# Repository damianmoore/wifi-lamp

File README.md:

# WiFi Lamp

A simple wifi-enabled lamp control board based on the ESP8266. It is intended
primarily to help retrofit existing LED lamps, giving them switching and dimming
functionality through a web browser or home automation system.

The project is based around the ESP8266-01 module as it is widely available,
small, very cheap, easily programmable, and directly connects to your existing
wifi network.

The included electronics files (schematic and PCB layout) are designed in KiCad.

An RS-232 USB-to-serial convertor is required for programming. If you use this
adaptor to power the device while programming, it must output 3.3V (not higher).

## Specifications

 * Input voltage: **3.3 – 15V**
 * LED PWM dimmer frequency: **1000 Hz**

## Components (BOM)

 * ESP8266-01 module
 * AMS1117 3.3V voltage regulator, SOT-223 package
 * BCP53 transistor, SOT-223 package
 * 2 × SMD SPST switches, ~6mm wide × ~3mm deep
 * Row of 4 header pins

## Renderings

## Schematic

## Overview of the layers used for PCB production

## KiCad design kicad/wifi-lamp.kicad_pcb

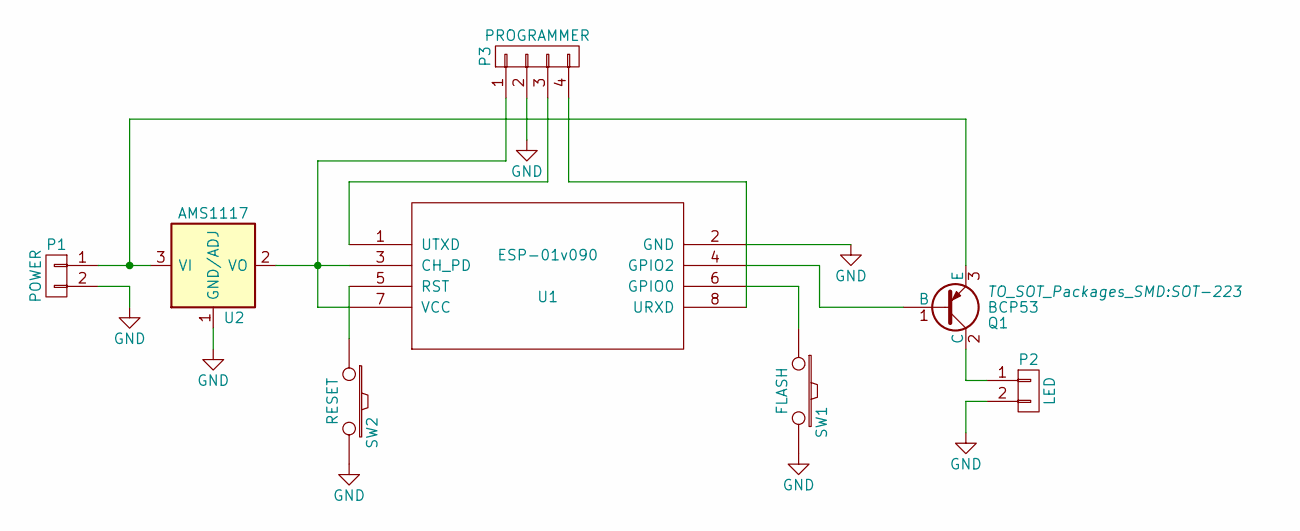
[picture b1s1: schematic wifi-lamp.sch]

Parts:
P1: POWER; WireConnection_1.50mmDrill
P2: LED; WireConnection_1.50mmDrill
P3: PROGRAMMER; Pin_Header_Straight_1x04
Q1: BCP53; SOT-223
SW1: FLASH; SW_SPST_REED_CT05-XXXX-G1
SW2: RESET; SW_SPST_REED_CT05-XXXX-G1
U1: ESP-01v090; ESP-01
U2: AMS1117; SOT-223

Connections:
GND: P1.2, P2.2, P3.2, SW1.2, SW2.2, U1.2 (GND), U2.1 (GND/ADJ)
unnamed: P1.1, Q1.3 (E), U2.3 (VI)
unnamed: P2.1, Q1.2 (C)
unnamed: P3.1, U1.3 (CH_PD), U1.7 (VCC), U2.2 (VO), U2.4 (VO)
unnamed: P3.3, U1.1 (UTXD)
unnamed: P3.4, U1.8 (URXD)
unnamed: Q1.1 (B), U1.4 (GPIO2)
unnamed: SW1.1, U1.6 (GPIO0)
unnamed: SW2.1, U1.5 (RST)

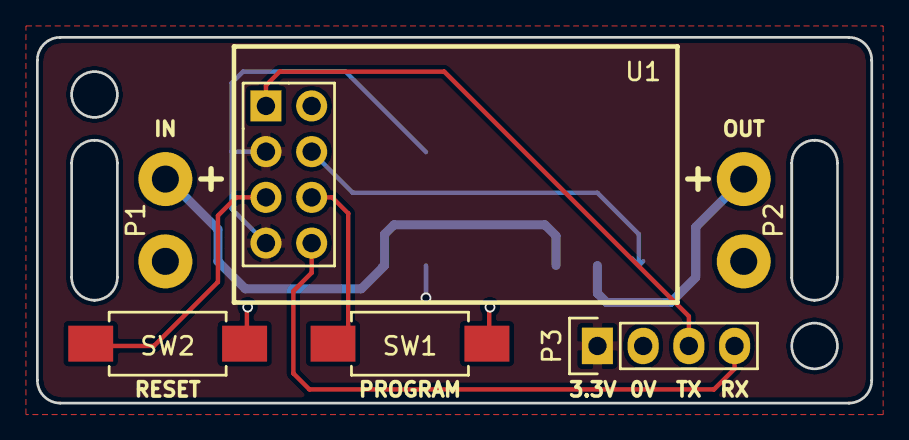
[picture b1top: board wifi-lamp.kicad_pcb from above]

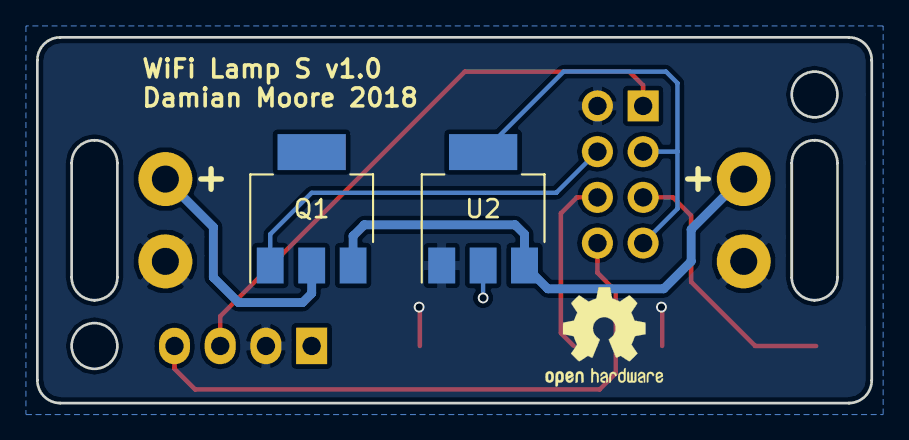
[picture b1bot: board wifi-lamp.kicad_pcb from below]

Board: 2 copper layers, 46.4 x 20.3 mm, 8 parts (2 on the bottom side), 9 nets.

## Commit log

2015-09-15 Light dimming controlled by HTML range slider
2015-09-28 Better styling and optimised for mobile
2015-09-28 Bulb images
2015-09-28 Full path of image URLs
2017-01-22 Fixed some styling
2018-02-10 Arduino code
2018-04-11 Tidied up Arduino code
2018-04-11 Added KiCad files for first version of the PCB that's being made
2018-04-12 Updated readme, added images, reorganised files
2018-04-12 Added license
